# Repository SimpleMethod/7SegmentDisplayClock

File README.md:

# 🕰️ 7 Segment display clock - simple segment clock based on the STM32 MCU using GPS time as a reference source.

# 🧗‍♂️Main milestones

1. Retrieving date and time from GPS and saving it to RTC.
2. Creating a PCB to display numbers using a 7 segment display.

# 🚀 Features
 1. Retrieving date and time from GPS.
2.  Information users by buzzer signals. 
3.  Setting alarms.
4.  Display date and time on 7 segment display.

# 🗺️ Technologies used in project 
 - Based on microcontroller STM32
- Used CD4511BE as BCD code decoder.
- Used GPS Ublox NEO-M8 as GPS signal receiver.
- Used DS3212 as RTC clock.
-  Development necessary libraries based on technical documentation,

# 🧪 Visualization PCB shield

# 🧪 Visualization PCB display top side

# 🧪 Visualization PCB display bottom side

# ⚡ Circuit diagrams

## 🎥  Video of the presentation:

[https://youtu.be/eESlLnk6x-c](https://youtu.be/eESlLnk6x-c)

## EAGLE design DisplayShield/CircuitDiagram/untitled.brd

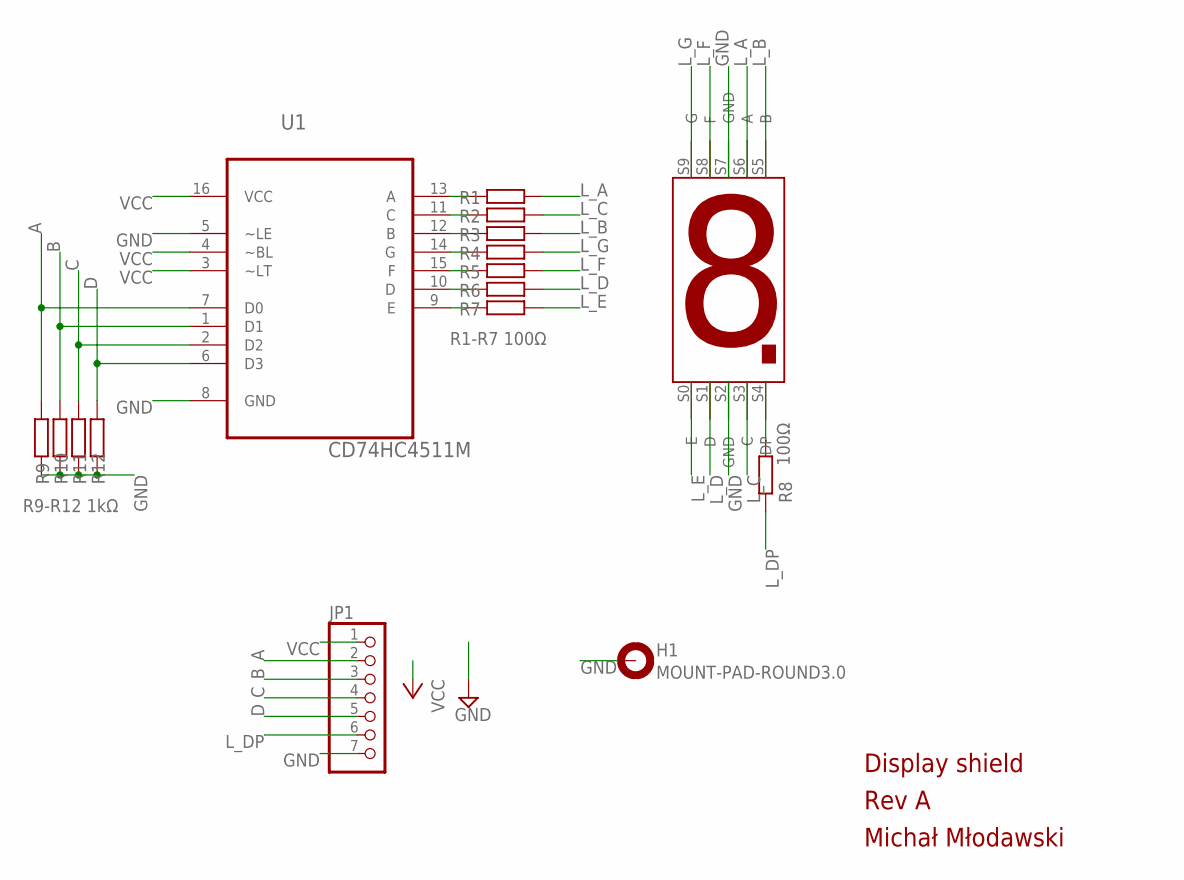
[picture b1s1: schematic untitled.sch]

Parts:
H1: MOUNT-PAD-ROUND3.0; 3,0-PAD
JP1: PINHD-1X7; 1X07
R1, R2, R3, R4, R5, R6, R7, R9, R10, R11, R12: R-EU_R1206; R1206
R8: 100Ω; R1206
U1: CD74HC4511M; SOIC127P600X175-16N
U$1: 7-SEGMENT-DISPLAY; 7-SEGMENTDISPLAY

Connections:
A: JP1.2, R9.2, U1.7 (D0)
B: JP1.3, R10.2, U1.1 (D1)
C: JP1.4, R11.2, U1.2 (D2)
D: JP1.5, R12.2, U1.6 (D3)
GND: H1.B3,0, JP1.7, R9.1, R10.1, R11.1, R12.1, U1.5 (~LE), U1.8 (GND), U$1.S2 (GND), U$1.S7 (GND)
L_A: R1.2, U$1.S6 (A)
L_B: R3.2, U$1.S5 (B)
L_C: R2.2, U$1.S3 (C)
L_D: R6.2, U$1.S1 (D)
L_DP: JP1.6, R8.1
L_E: R7.2, U$1.S0 (E)
L_F: R5.2, U$1.S8 (F)
L_G: R4.2, U$1.S9 (G)
unnamed: R1.1, U1.13 (A)
unnamed: R2.1, U1.11 (C)
unnamed: R3.1, U1.12 (B)
unnamed: R4.1, U1.14 (G)
unnamed: R5.1, U1.15 (F)
unnamed: R6.1, U1.10 (D)
unnamed: R7.1, U1.9 (E)
unnamed: R8.2, U$1.S4 (DP)
VCC: JP1.1, U1.3 (~LT), U1.4 (~BL), U1.16 (VCC)

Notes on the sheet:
R1-R7 100Ω
R9-R12 1kΩ
Michał Młodawski
Rev A
Display shield

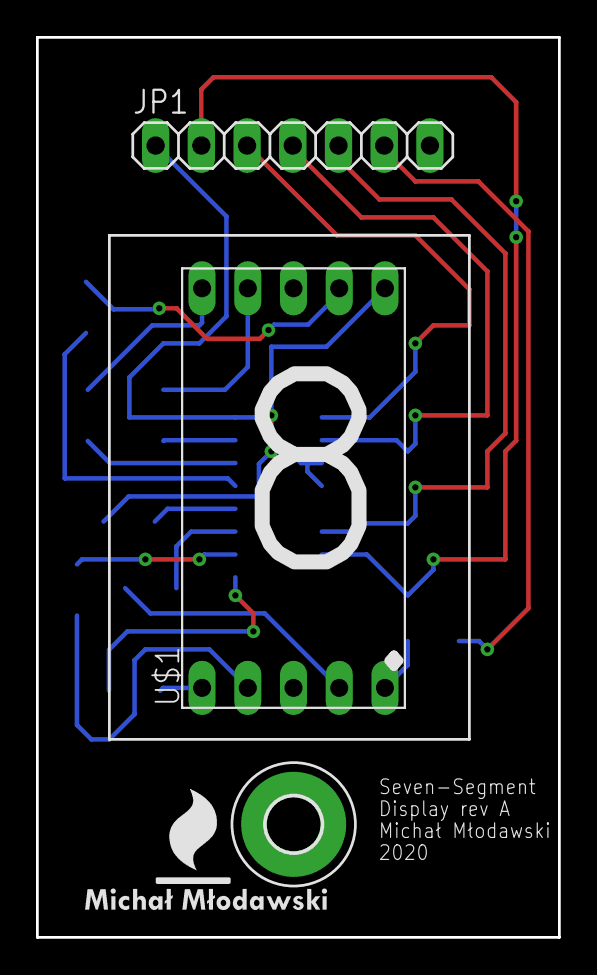
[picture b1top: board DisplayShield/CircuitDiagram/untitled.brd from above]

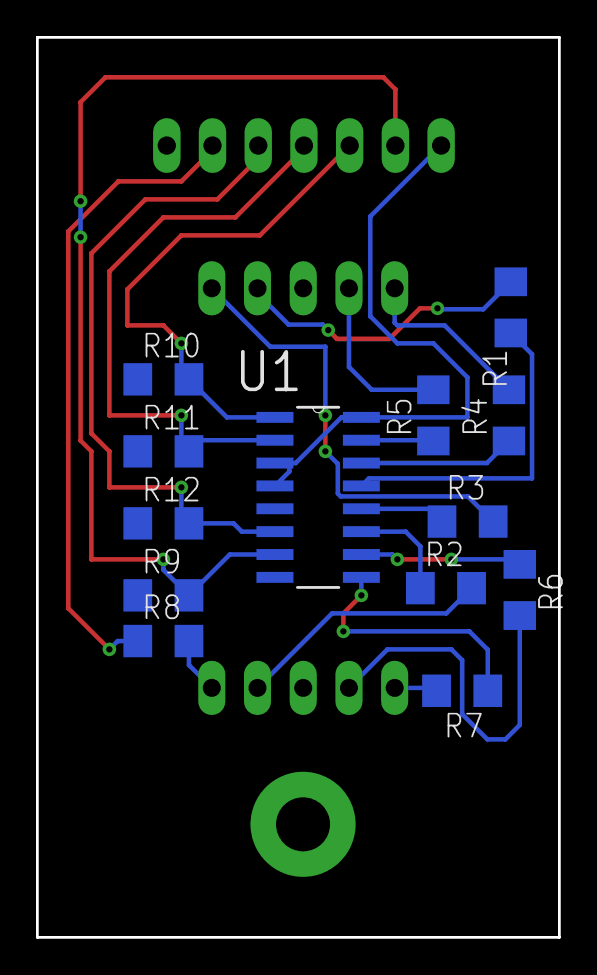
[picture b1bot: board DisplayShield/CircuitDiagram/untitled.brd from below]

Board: 2 copper layers, 29.0 x 50.0 mm, 16 parts (13 on the bottom side), 22 nets.

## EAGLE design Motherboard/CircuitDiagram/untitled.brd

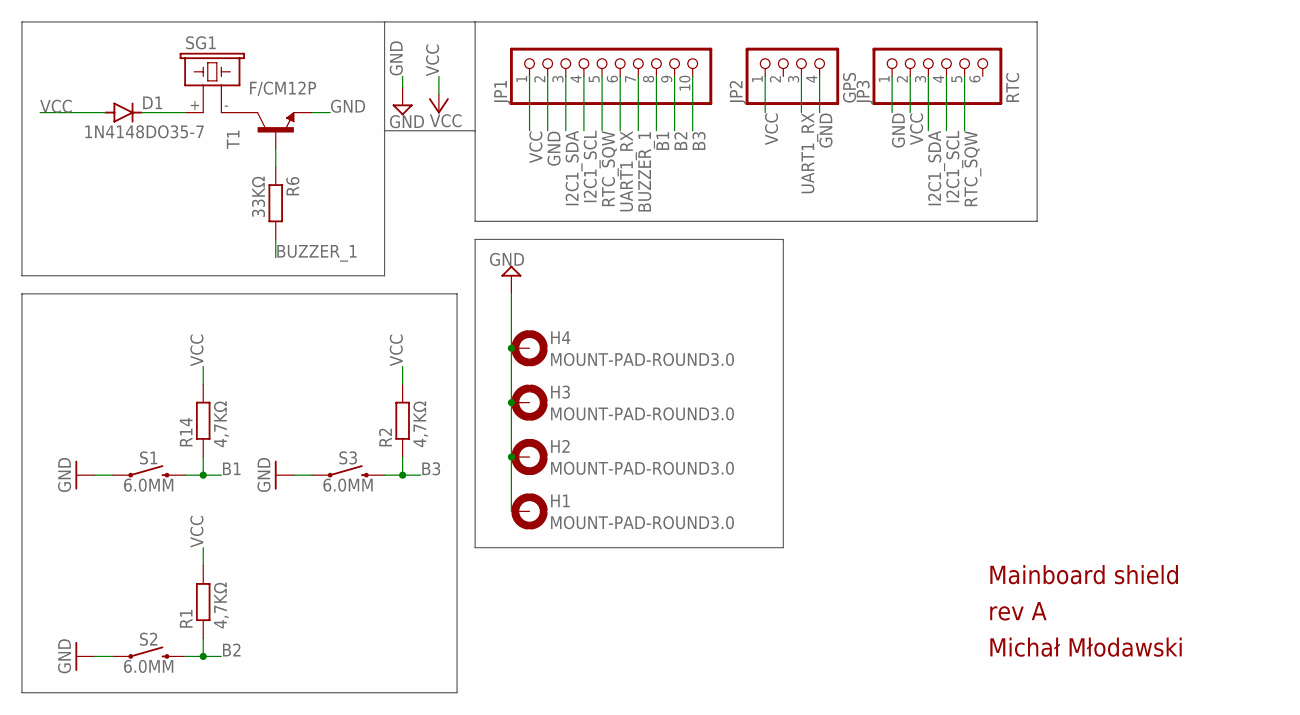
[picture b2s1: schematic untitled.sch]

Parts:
D1: 1N4148DO35-7; DO35-7
H1, H2, H3, H4: MOUNT-PAD-ROUND3.0; 3,0-PAD
JP1: PINHD-1X10; 1X10
JP2: GPS; 1X04
JP3: RTC; 1X06
R1, R2, R14: 4,7KΩ; R1206
R6: 33KΩ; R1206
S1, S2, S3: 6.0MM; TACTILE_SWITCH_PTH_6.0MM
SG1: F/CM12P
T1: BC548-NPN-TO92-CBE; TO92-CBE

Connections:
B1: JP1.8, R14.1, S1.3 (2)
B2: JP1.9, R1.1, S2.3 (2)
B3: JP1.10, R2.1, S3.3 (2)
BUZZER_1: JP1.7, R6.2
GND: H1.B3,0, H2.B3,0, H3.B3,0, H4.B3,0, JP1.2, JP2.4, JP3.1, S1.1, S2.1, S3.1, T1.E
I2C1_SCL: JP1.4, JP3.4
I2C1_SDA: JP1.3, JP3.3
unnamed: D1.C, SG1.+ (1)
unnamed: SG1.- (2), T1.C
unnamed: R6.1, T1.B
RTC_SQW: JP1.5, JP3.5
UART1_RX: JP1.6, JP2.3
VCC: D1.A, JP1.1, JP2.1, JP3.2, R1.2, R2.2, R14.2

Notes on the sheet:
Michał Młodawski
rev A
Mainboard shield

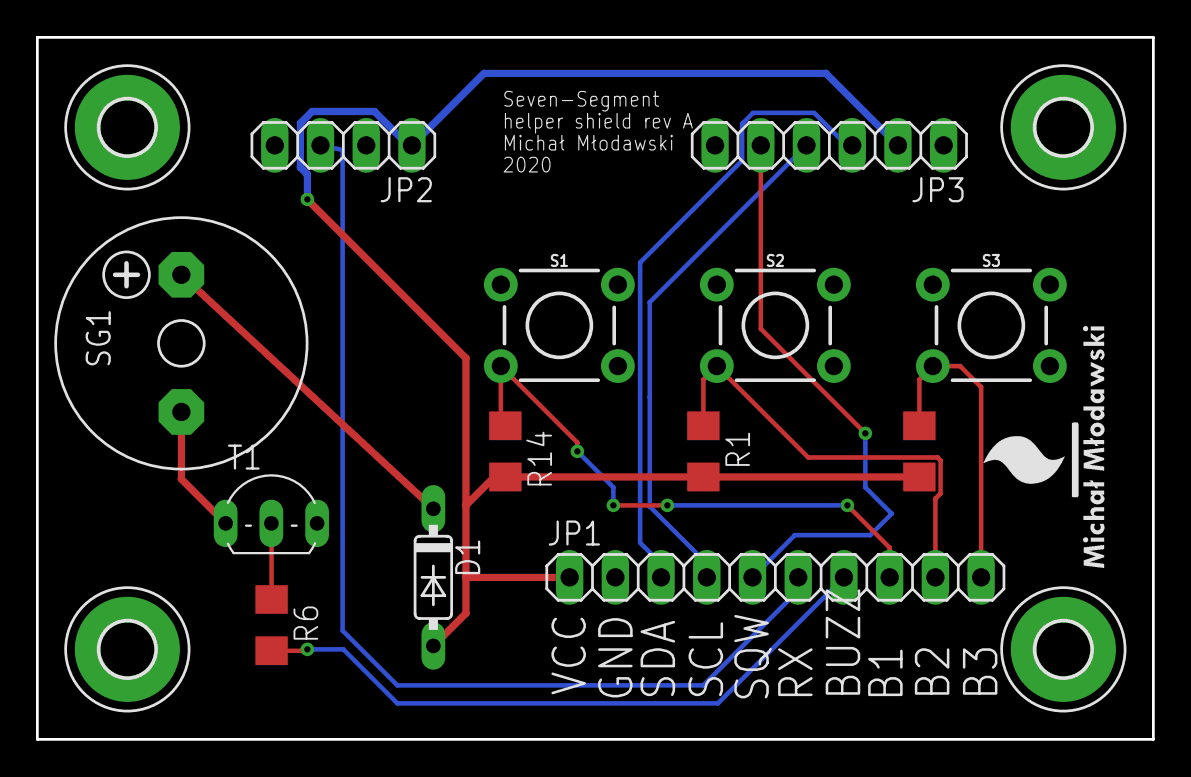
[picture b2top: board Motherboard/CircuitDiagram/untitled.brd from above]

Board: 2 copper layers, 62.0 x 39.0 mm, 17 parts (0 on the bottom side), 13 nets.

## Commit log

2020-06-04 Adding calendar support

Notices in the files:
parts and their libraries:
SparkFun-Switches: Licensing: Creative Commons ShareAlike 4.0 International - https://creativecommons.org/licenses/by-sa/4.0
